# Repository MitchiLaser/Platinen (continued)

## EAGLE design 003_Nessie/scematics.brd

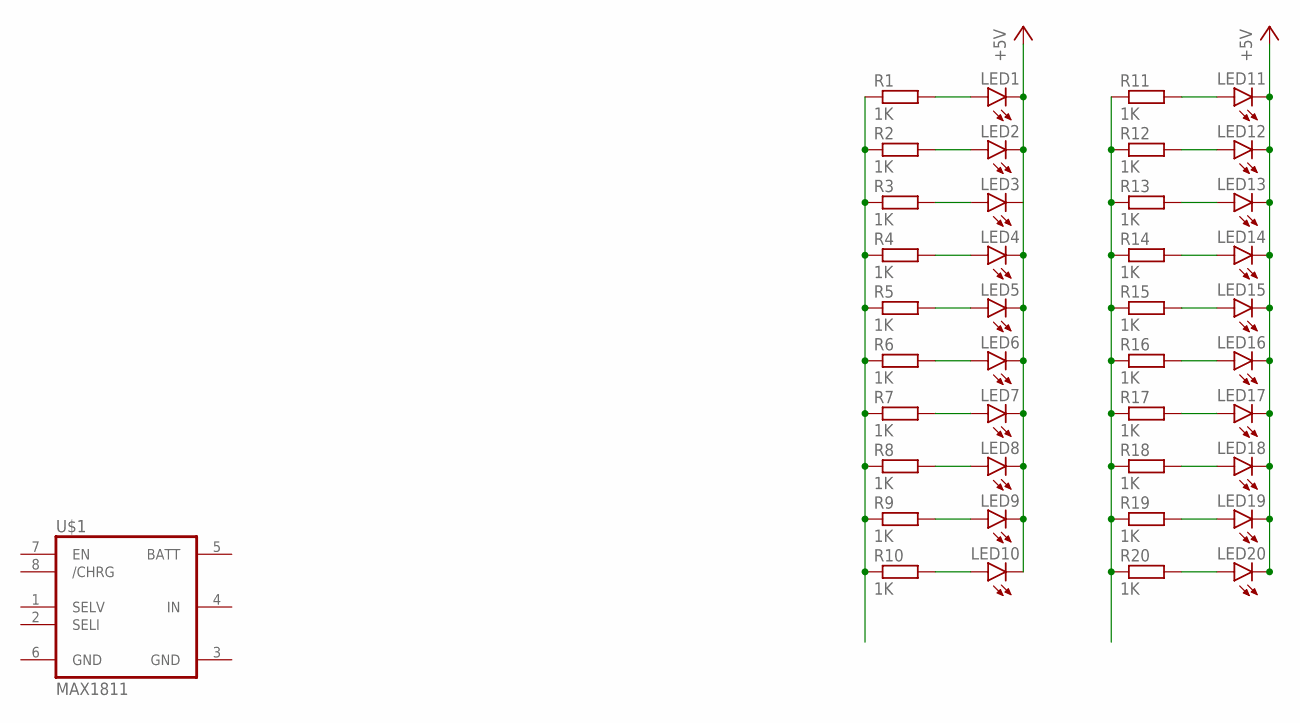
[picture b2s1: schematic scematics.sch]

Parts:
LED1, LED2, LED3, LED4, LED5, LED6, LED7, LED8, LED9, LED10, LED11, LED12, LED13, LED14, LED15, LED16, LED17, LED18, LED19, LED20: LEDCHIPLED_0805; CHIPLED_0805
R1, R2, R3, R4, R5, R6, R7, R8, R9, R10, R11, R12, R13, R14, R15, R16, R17, R18, R19, R20: 1K; R0805
U$1: MAX1811; SO08

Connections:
+5V: LED1.C, LED2.C, LED4.C, LED5.C, LED6.C, LED7.C, LED8.C, LED9.C, LED10.C, LED11.C, LED12.C, LED13.C, LED14.C, LED15.C, LED16.C, LED17.C, LED18.C, LED19.C, LED20.C
GND: U$1.3 (GND), U$1.6 (GND)
IN: U$1.4 (IN)
unnamed: LED1.A, R1.2
unnamed: LED2.A, R2.2
unnamed: LED3.A, R3.2
unnamed: LED4.A, R4.2
unnamed: LED5.A, R5.2
unnamed: LED6.A, R6.2
unnamed: LED7.A, R7.2
unnamed: LED8.A, R8.2
unnamed: LED9.A, R9.2
unnamed: LED10.A, R10.2
unnamed: LED11.A, R11.2
unnamed: LED12.A, R12.2
unnamed: LED13.A, R13.2
unnamed: LED14.A, R14.2
unnamed: LED15.A, R15.2
unnamed: LED16.A, R16.2
unnamed: LED17.A, R17.2
unnamed: LED18.A, R18.2
unnamed: LED19.A, R19.2
unnamed: LED20.A, R20.2
unnamed: R1.1, R2.1, R3.1, R4.1, R5.1, R6.1, R7.1, R8.1, R9.1, R10.1
unnamed: R11.1, R12.1, R13.1, R14.1, R15.1, R16.1, R17.1, R18.1, R19.1, R20.1

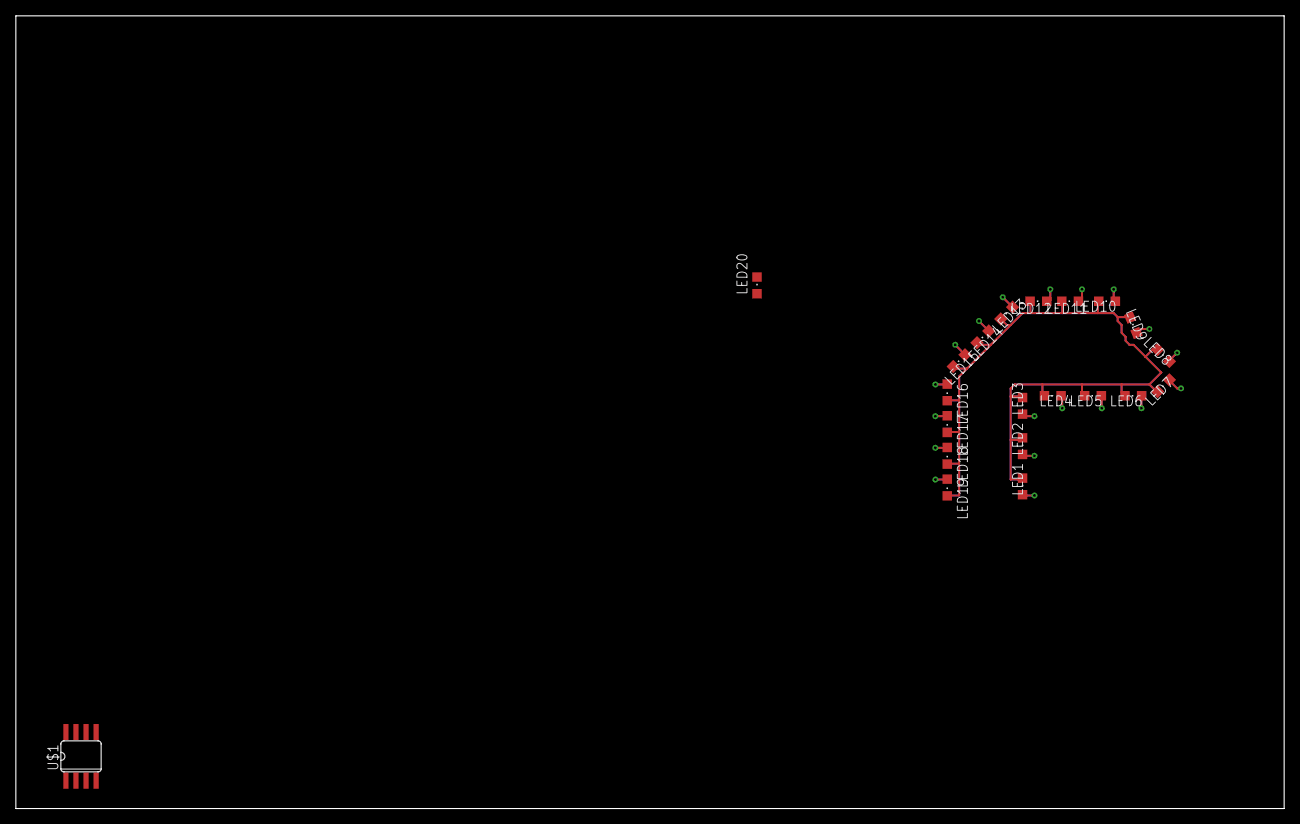
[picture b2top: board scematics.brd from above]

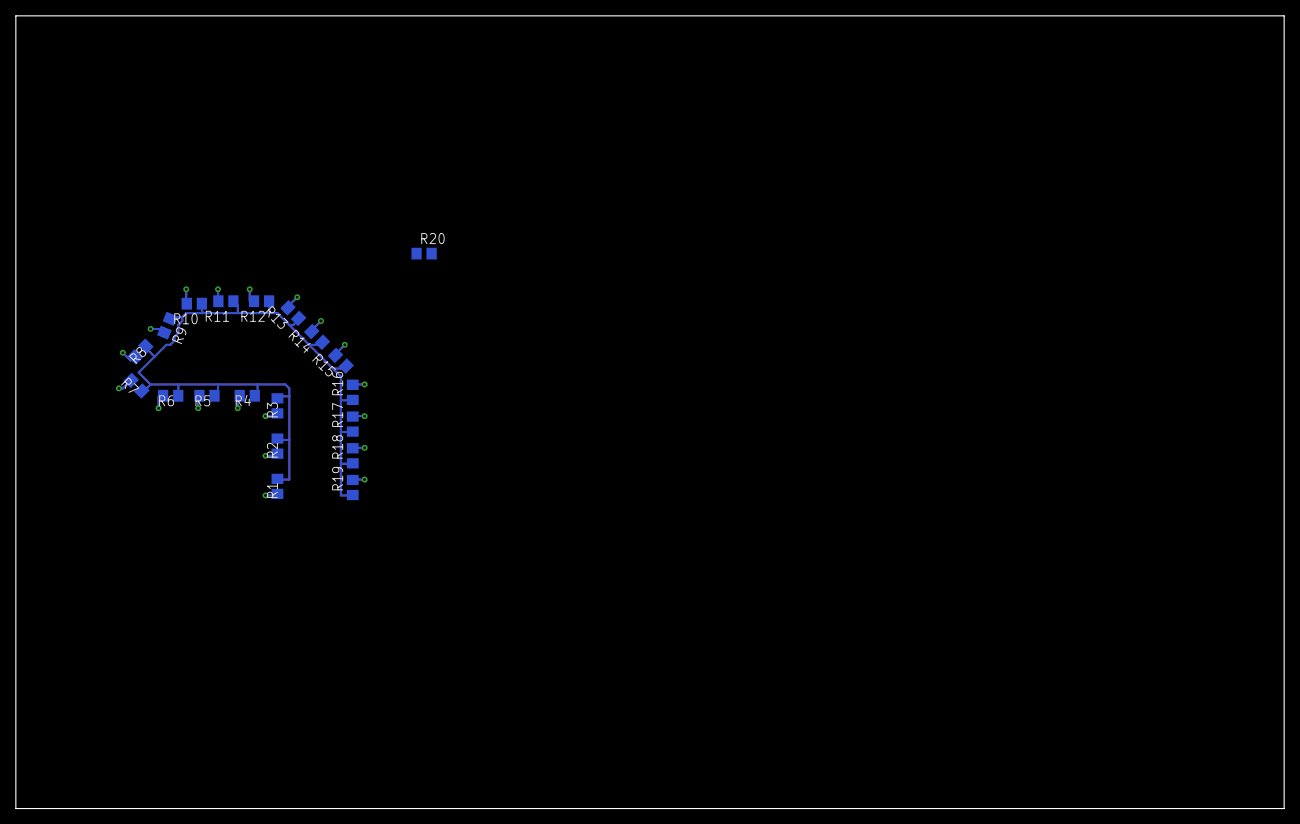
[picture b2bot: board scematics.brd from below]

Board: 2 copper layers, 160.0 x 100.0 mm, 41 parts (20 on the bottom side), 24 nets.

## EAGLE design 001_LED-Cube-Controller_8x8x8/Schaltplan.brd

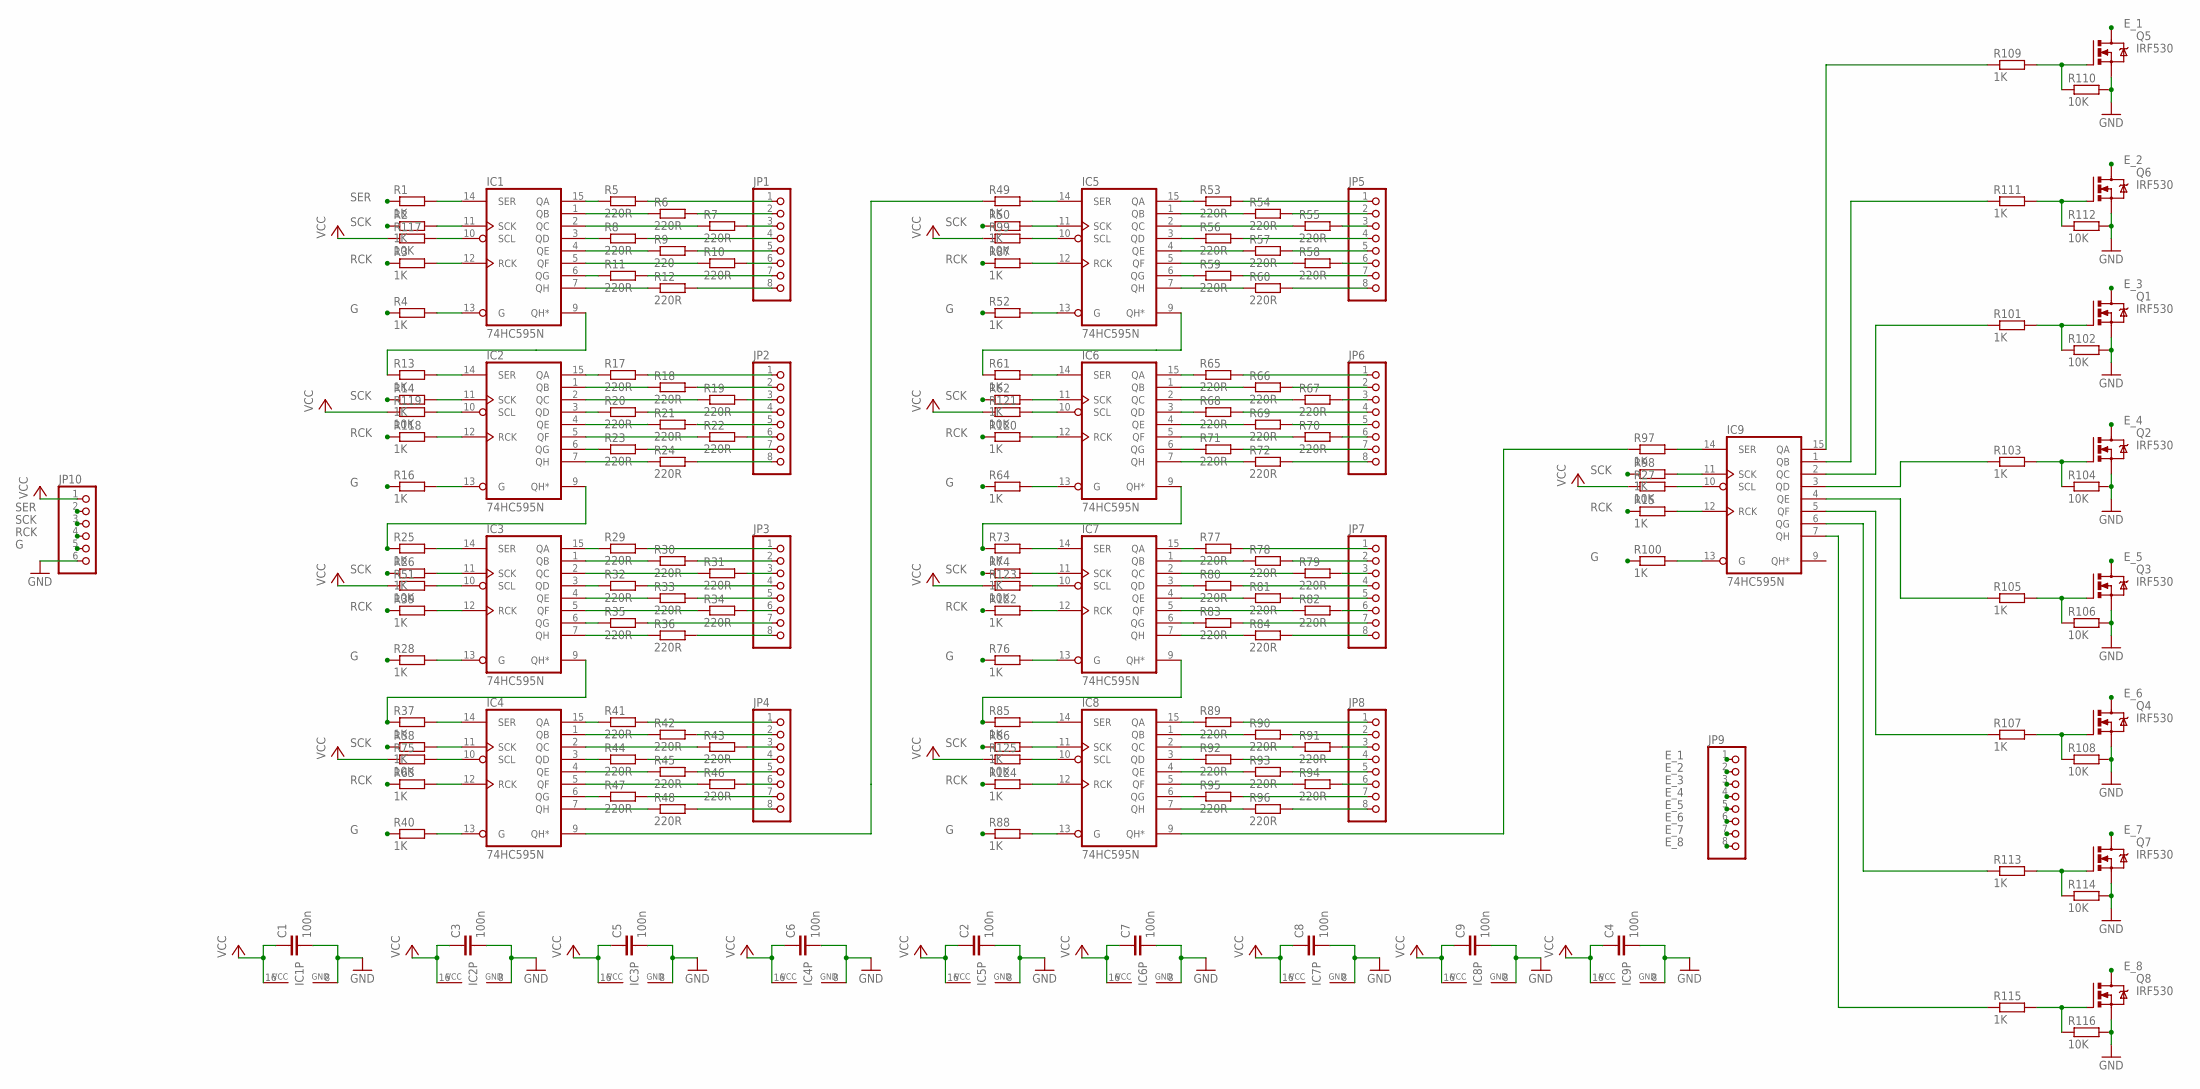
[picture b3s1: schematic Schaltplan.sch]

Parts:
C1, C2, C3, C4, C5, C6, C7, C8, C9: 100n; C5B3
IC1, IC2, IC3, IC4, IC5, IC6, IC7, IC8, IC9: 74HC595N; DIL16
JP1, JP2, JP3, JP4, JP5, JP6, JP7, JP8, JP9: PINHD-1X8; 1X08
JP10: PINHD-1X6; 1X06
Q1, Q2, Q3, Q4, Q5, Q6, Q7, Q8: IRF530; TO220BV
R1, R2, R3, R4, R13, R14, R15, R16, R25, R26, R28, R37, R38, R39, R40, R49, R50, R52, R61, R62, R63, R64, R73, R74, R76, R85, R86, R87, R88, R97, R98, R100, R101, R103, R105, R107, R109, R111, R113, R115, R118, R120, R122, R124: 1K; 0207/10
R5, R6, R7, R8, R10, R11, R12, R17, R18, R19, R20, R21, R22, R23, R24, R29, R30, R31, R32, R33, R34, R35, R36, R41, R42, R43, R44, R45, R46, R47, R48, R53, R54, R55, R56, R57, R58, R59, R60, R65, R66, R67, R68, R69, R70, R71, R72, R77, R78, R79, R80, R81, R82, R83, R84, R89, R90, R91, R92, R93, R94, R95, R96: 220R; 0207/10
R9: 220; 0207/10
R27, R51, R75, R99, R102, R104, R106, R108, R110, R112, R114, R116, R117, R119, R121, R123, R125: 10K; 0207/10

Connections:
E_1: JP9.1, Q5.D
E_2: JP9.2, Q6.D
E_3: JP9.3, Q1.D
E_4: JP9.4, Q2.D
E_5: JP9.5, Q3.D
E_6: JP9.6, Q4.D
E_7: JP9.7, Q7.D
E_8: JP9.8, Q8.D
G: JP10.5, R4.1, R16.1, R28.1, R40.1, R52.1, R64.1, R76.1, R88.1, R100.1
GND: C1.2, C2.2, C3.2, C4.2, C5.2, C6.2, C7.2, C8.2, C9.2, IC1.8 (GND), IC2.8 (GND), IC3.8 (GND), IC4.8 (GND), IC5.8 (GND), IC6.8 (GND), IC7.8 (GND), IC8.8 (GND), IC9.8 (GND), JP10.6, Q1.S, Q2.S, Q3.S, Q4.S, Q5.S, Q6.S, Q7.S, Q8.S, R102.2, R104.2, R106.2, R108.2, R110.2, R112.2, R114.2, R116.2
unnamed: IC1.14 (SER), R1.2
unnamed: IC1.11 (SCK), R2.2
unnamed: IC1.12 (RCK), R3.2
unnamed: IC1.13 (G), R4.2
unnamed: JP1.1, R5.2
unnamed: IC1.15 (QA), R5.1
unnamed: IC1.1 (QB), R6.1
unnamed: JP1.2, R6.2
unnamed: JP1.3, R7.2
unnamed: IC1.2 (QC), R7.1
unnamed: IC1.3 (QD), R8.1
unnamed: JP1.4, R8.2
unnamed: JP1.5, R9.2
unnamed: IC1.4 (QE), R9.1
unnamed: IC1.5 (QF), R10.1
unnamed: JP1.6, R10.2
unnamed: JP1.7, R11.2
unnamed: IC1.6 (QG), R11.1
unnamed: IC1.7 (QH), R12.1
unnamed: JP1.8, R12.2
unnamed: IC2.14 (SER), R13.2
unnamed: IC2.11 (SCK), R14.2
unnamed: IC2.10 (SCL), R119.2
unnamed: IC2.13 (G), R16.2
unnamed: JP2.1, R17.2
unnamed: IC2.15 (QA), R17.1
unnamed: IC2.1 (QB), R18.1
unnamed: JP2.2, R18.2
unnamed: JP2.3, R19.2
unnamed: IC2.2 (QC), R19.1
unnamed: IC2.3 (QD), R20.1
unnamed: JP2.4, R20.2
unnamed: JP2.5, R21.2
unnamed: IC2.4 (QE), R21.1
unnamed: IC2.5 (QF), R22.1
unnamed: JP2.6, R22.2
unnamed: JP2.7, R23.2
unnamed: IC2.6 (QG), R23.1
unnamed: IC2.7 (QH), R24.1
unnamed: JP2.8, R24.2
unnamed: IC3.14 (SER), R25.2
unnamed: IC3.11 (SCK), R26.2
unnamed: IC3.12 (RCK), R39.2
unnamed: IC3.13 (G), R28.2
unnamed: JP3.1, R29.2
unnamed: IC3.15 (QA), R29.1
unnamed: IC3.1 (QB), R30.1
unnamed: JP3.2, R30.2
unnamed: JP3.3, R31.2
unnamed: IC3.2 (QC), R31.1
unnamed: IC3.3 (QD), R32.1
unnamed: JP3.4, R32.2
unnamed: JP3.5, R33.2
unnamed: IC3.4 (QE), R33.1
unnamed: IC3.5 (QF), R34.1
unnamed: JP3.6, R34.2
unnamed: JP3.7, R35.2
unnamed: IC3.6 (QG), R35.1
unnamed: IC3.7 (QH), R36.1
unnamed: JP3.8, R36.2
unnamed: IC4.14 (SER), R37.2
unnamed: IC4.11 (SCK), R38.2
unnamed: IC3.10 (SCL), R51.2
unnamed: IC4.13 (G), R40.2
unnamed: JP4.1, R41.2
unnamed: IC4.15 (QA), R41.1
unnamed: IC4.1 (QB), R42.1
unnamed: JP4.2, R42.2
unnamed: JP4.3, R43.2
unnamed: IC4.2 (QC), R43.1
unnamed: IC4.3 (QD), R44.1
unnamed: JP4.4, R44.2
unnamed: JP4.5, R45.2
unnamed: IC4.4 (QE), R45.1
unnamed: IC4.5 (QF), R46.1
unnamed: JP4.6, R46.2
unnamed: JP4.7, R47.2
unnamed: IC4.6 (QG), R47.1
unnamed: IC4.7 (QH), R48.1
unnamed: JP4.8, R48.2
unnamed: IC5.14 (SER), R49.2
unnamed: IC5.11 (SCK), R50.2
unnamed: IC4.10 (SCL), R75.2
unnamed: IC5.13 (G), R52.2
unnamed: JP5.1, R53.2
unnamed: IC5.15 (QA), R53.1
unnamed: IC5.1 (QB), R54.1
unnamed: JP5.2, R54.2
unnamed: JP5.3, R55.2
unnamed: IC5.2 (QC), R55.1
unnamed: IC5.3 (QD), R56.1
unnamed: JP5.4, R56.2
unnamed: JP5.5, R57.2
unnamed: IC5.4 (QE), R57.1
unnamed: IC5.5 (QF), R58.1
unnamed: JP5.6, R58.2
unnamed: JP5.7, R59.2
unnamed: IC5.6 (QG), R59.1
unnamed: IC5.7 (QH), R60.1
unnamed: JP5.8, R60.2
unnamed: IC6.14 (SER), R61.2
unnamed: IC6.11 (SCK), R62.2
unnamed: IC4.12 (RCK), R63.2
unnamed: IC6.13 (G), R64.2
unnamed: JP6.1, R65.2
unnamed: IC6.15 (QA), R65.1
unnamed: IC6.1 (QB), R66.1
unnamed: JP6.2, R66.2
unnamed: JP6.3, R67.2
unnamed: IC6.2 (QC), R67.1
unnamed: IC6.3 (QD), R68.1
unnamed: JP6.4, R68.2
unnamed: JP6.5, R69.2
unnamed: IC6.4 (QE), R69.1
unnamed: IC6.5 (QF), R70.1
unnamed: JP6.6, R70.2
unnamed: JP6.7, R71.2
unnamed: IC6.6 (QG), R71.1
unnamed: IC6.7 (QH), R72.1
unnamed: JP6.8, R72.2
unnamed: IC7.14 (SER), R73.2
unnamed: IC7.11 (SCK), R74.2
unnamed: IC6.10 (SCL), R121.2
unnamed: IC7.13 (G), R76.2
unnamed: JP7.1, R77.2
unnamed: IC7.15 (QA), R77.1
unnamed: IC7.1 (QB), R78.1
unnamed: JP7.2, R78.2
unnamed: JP7.3, R79.2
unnamed: IC7.2 (QC), R79.1
unnamed: IC7.3 (QD), R80.1
unnamed: JP7.4, R80.2
unnamed: JP7.5, R81.2
unnamed: IC7.4 (QE), R81.1
unnamed: IC7.5 (QF), R82.1
unnamed: JP7.6, R82.2
unnamed: JP7.7, R83.2
unnamed: IC7.6 (QG), R83.1
unnamed: IC7.7 (QH), R84.1
unnamed: JP7.8, R84.2
unnamed: IC8.14 (SER), R85.2
unnamed: IC8.11 (SCK), R86.2
unnamed: IC6.12 (RCK), R120.2
unnamed: IC8.13 (G), R88.2
unnamed: JP8.1, R89.2
unnamed: IC8.15 (QA), R89.1
unnamed: IC8.1 (QB), R90.1
unnamed: JP8.2, R90.2
unnamed: JP8.3, R91.2
unnamed: IC8.2 (QC), R91.1
unnamed: IC8.3 (QD), R92.1
unnamed: JP8.4, R92.2
unnamed: JP8.5, R93.2
unnamed: IC8.4 (QE), R93.1
unnamed: IC8.5 (QF), R94.1
unnamed: JP8.6, R94.2
unnamed: JP8.7, R95.2
unnamed: IC8.6 (QG), R95.1
unnamed: IC8.7 (QH), R96.1
unnamed: JP8.8, R96.2
unnamed: IC9.14 (SER), R97.2
unnamed: IC9.11 (SCK), R98.2
unnamed: IC7.10 (SCL), R123.2
unnamed: IC9.13 (G), R100.2
unnamed: Q1.G, R101.2, R102.1
unnamed: Q2.G, R103.2, R104.1
unnamed: Q3.G, R105.2, R106.1
unnamed: Q4.G, R107.2, R108.1
unnamed: Q5.G, R109.2, R110.1
unnamed: Q6.G, R111.2, R112.1
unnamed: Q7.G, R113.2, R114.1
unnamed: Q8.G, R115.2, R116.1
unnamed: IC9.15 (QA), R109.1
unnamed: IC9.1 (QB), R111.1
unnamed: IC9.2 (QC), R101.1
unnamed: IC9.3 (QD), R103.1
unnamed: IC9.4 (QE), R105.1
unnamed: IC9.5 (QF), R107.1
unnamed: IC9.6 (QG), R113.1
unnamed: IC9.7 (QH), R115.1
unnamed: IC8.9 (QH*), R97.1
unnamed: IC1.9 (QH*), R13.1
unnamed: IC4.9 (QH*), R49.1
unnamed: IC5.9 (QH*), R61.1
unnamed: IC1.10 (SCL), R117.2
unnamed: IC2.12 (RCK), R118.2
unnamed: IC7.12 (RCK), R122.2
unnamed: IC8.10 (SCL), R125.2
unnamed: IC8.12 (RCK), R124.2
unnamed: IC5.10 (SCL), R99.2
unnamed: IC5.12 (RCK), R87.2
unnamed: IC9.10 (SCL), R27.2
unnamed: IC9.12 (RCK), R15.2
RCK: JP10.4, R3.1, R15.1, R39.1, R63.1, R87.1, R118.1, R120.1, R122.1, R124.1
SCK: JP10.3, R2.1, R14.1, R26.1, R38.1, R50.1, R62.1, R74.1, R86.1, R98.1
SER: JP10.2, R1.1
SER1: IC2.9 (QH*), R25.1
SER2: IC3.9 (QH*), R37.1
SER3: IC6.9 (QH*), R73.1
SER4: IC7.9 (QH*), R85.1
VCC: C1.1, C2.1, C3.1, C4.1, C5.1, C6.1, C7.1, C8.1, C9.1, IC1.16 (VCC), IC2.16 (VCC), IC3.16 (VCC), IC4.16 (VCC), IC5.16 (VCC), IC6.16 (VCC), IC7.16 (VCC), IC8.16 (VCC), IC9.16 (VCC), JP10.1, R27.1, R51.1, R75.1, R99.1, R117.1, R119.1, R121.1, R123.1, R125.1

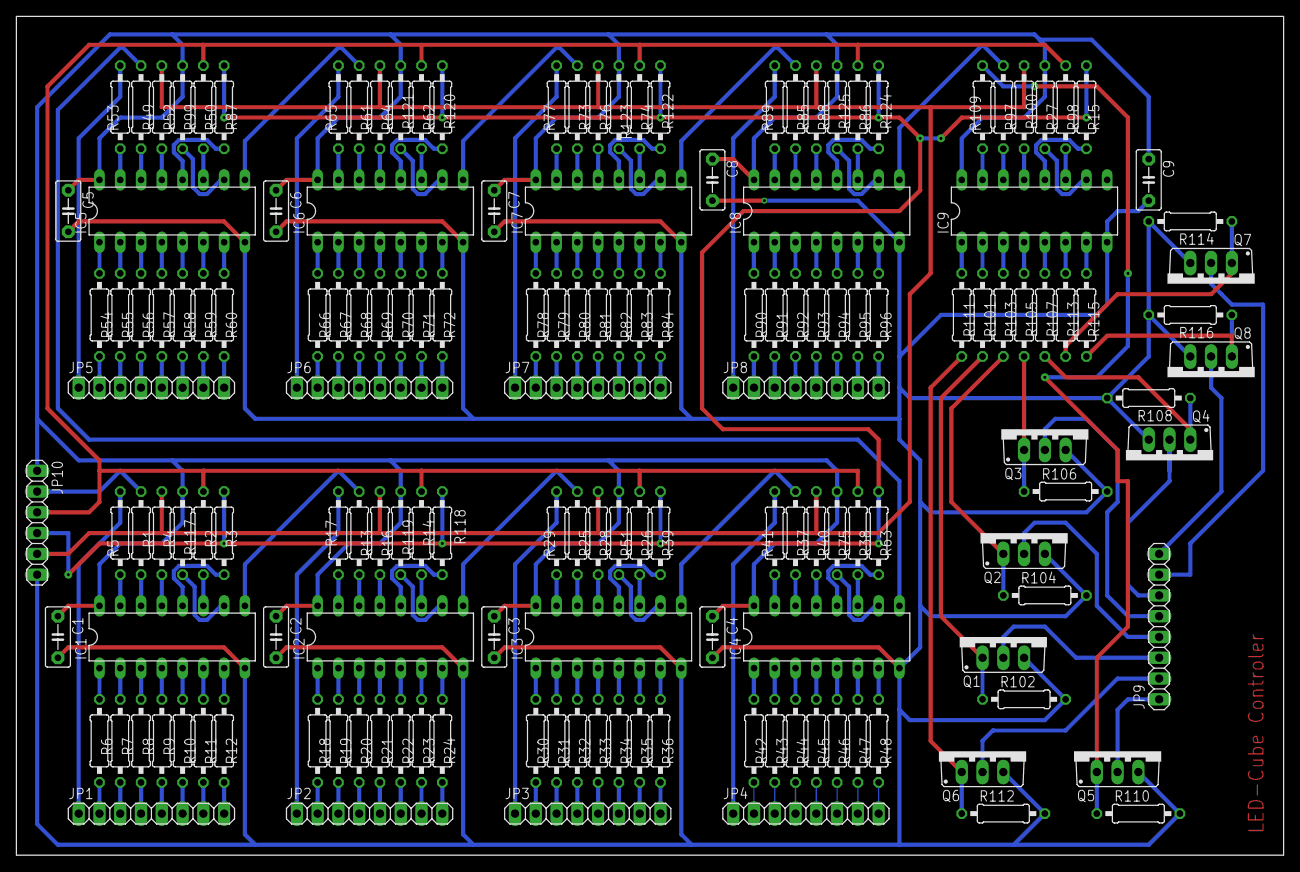
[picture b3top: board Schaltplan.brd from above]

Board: 2 copper layers, 154.9 x 102.5 mm, 161 parts (0 on the bottom side), 211 nets.

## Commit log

2020-01-30 LED-Cube Treiber hinzugefügt
2020-03-06 Added Lemon (Slave) PCB
2021-03-17 extracted pattern
2021-04-19 Nessie anfang
2021-04-28 Master-Controller für das HoLi-Light
2021-05-03 Bewässerungssystem für Pfanzen hinzugefügt
2021-06-17 lemon-light korrektur-board
2021-06-17 fixed error in lemon-light slave controller
2021-10-17 update lemon light main controller
2021-10-26 LED Matrix PCB
